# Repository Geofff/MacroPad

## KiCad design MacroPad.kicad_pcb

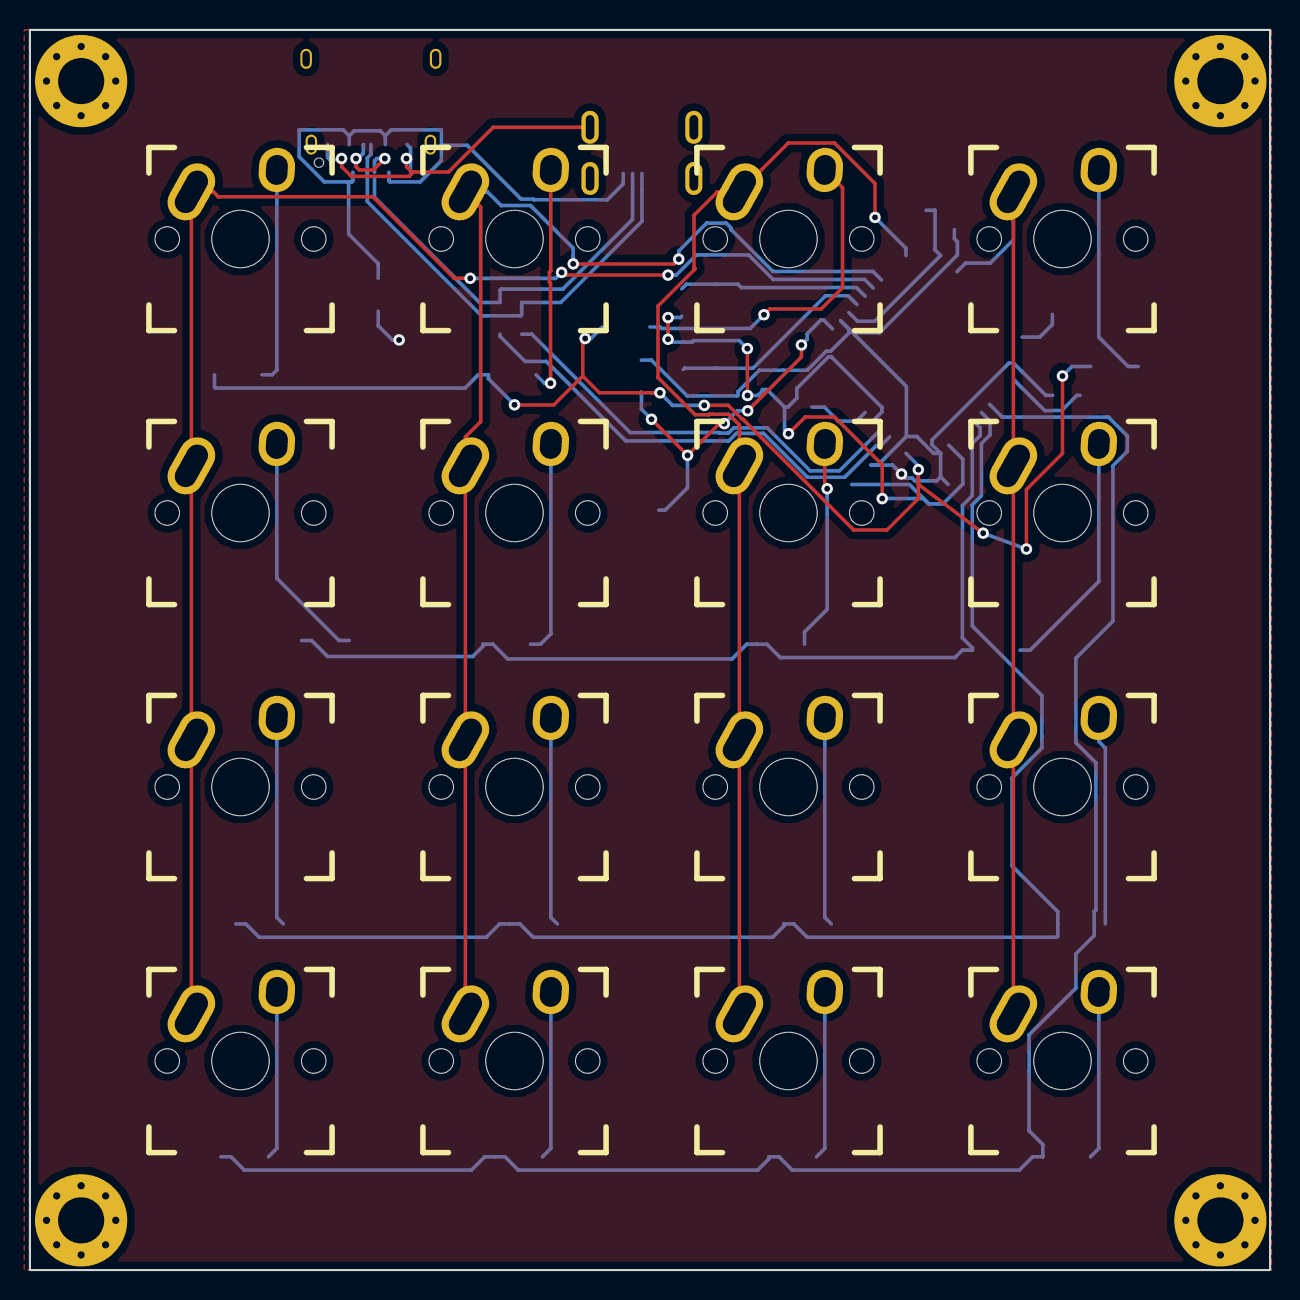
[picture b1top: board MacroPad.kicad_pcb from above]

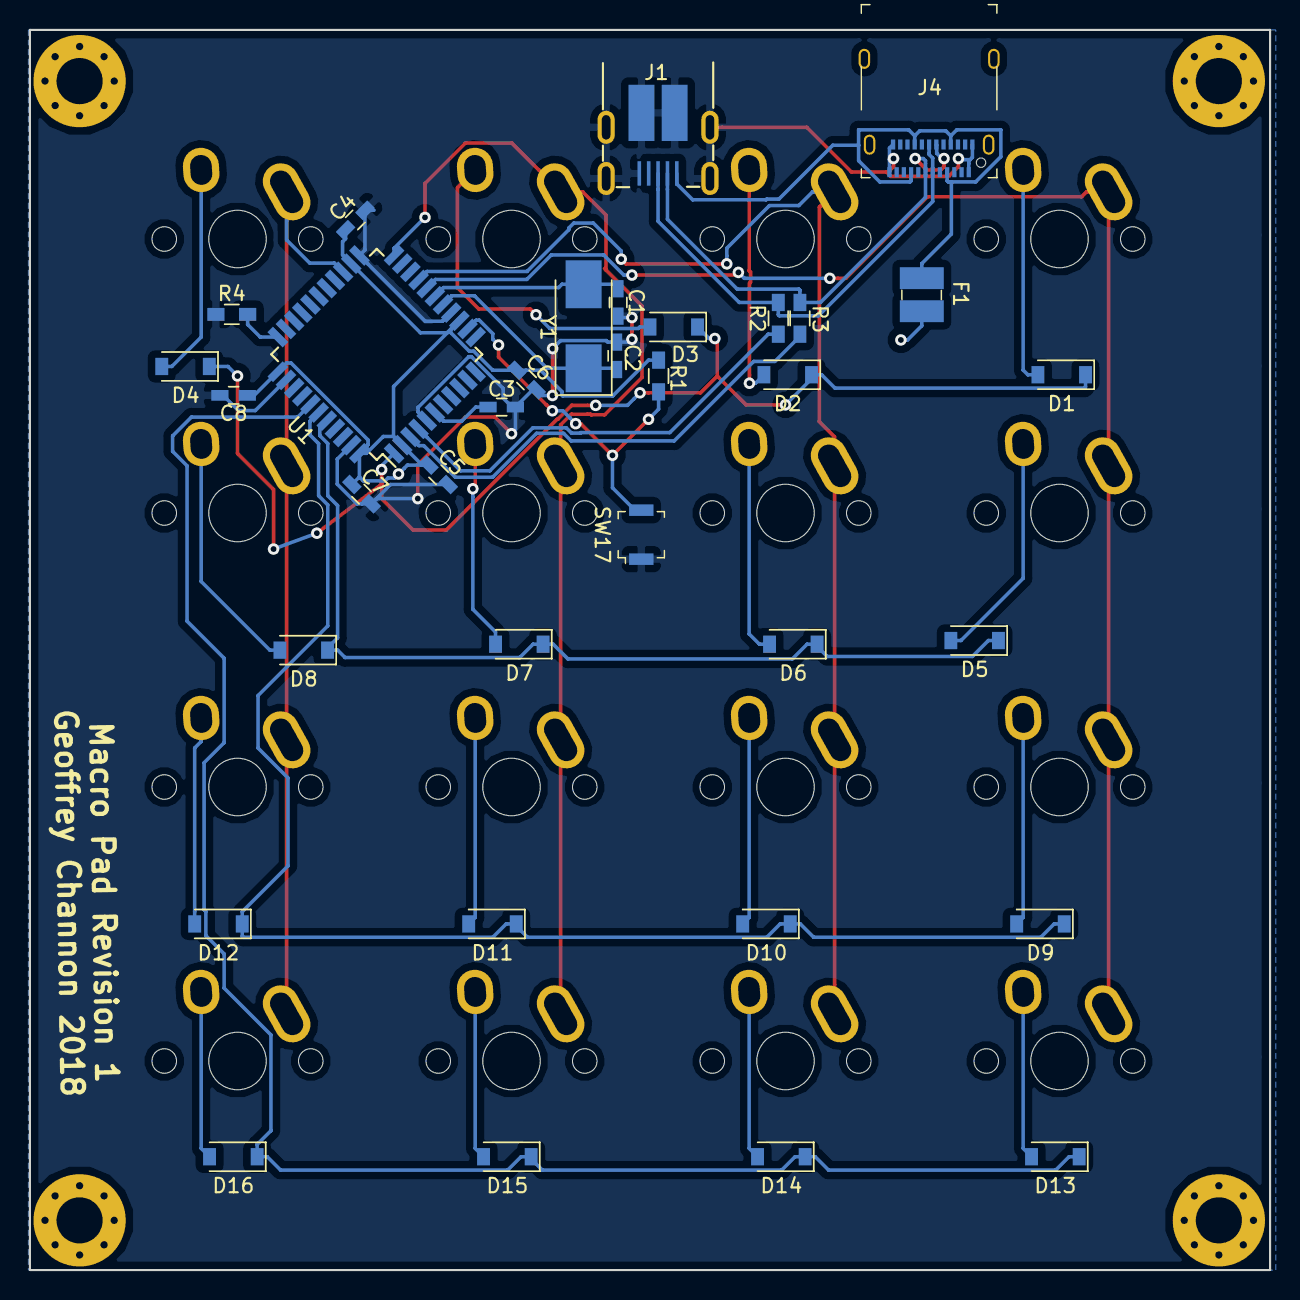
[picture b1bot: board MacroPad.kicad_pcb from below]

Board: 2 copper layers, 86.0 x 86.0 mm, 50 parts (34 on the bottom side), 36 nets.

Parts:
C1, C2: 18pF; C_0603_HandSoldering
C3, C4, C5, C6, C7, C8: 0.1uF; C_0603_HandSoldering
D1, D2, D3, D4, D5, D6, D7, D8, D9, D10, D11, D12, D13, D14, D15, D16: D; D_SOD-123
F1: 500mA; 1210
J1: UJ2-MIBH-4-SMT-TR; USB_Micro_B_Male_UJ2-MIBH-4-SMT-TR
J4: 12401610E4_2A; USB_Type_C_Female__12401610E4_2A
R1, R4: 10k; R_0603_HandSoldering
R2, R3: 22; R_0603_HandSoldering
SW1, SW2, SW3, SW4, SW5, SW6, SW7, SW8, SW9, SW10, SW11, SW12, SW13, SW14, SW15, SW16: SW_Push; Mx_Alps_100
SW17: SW_Push; Switch_Tactile_SMD_B3U-1000P
U1: ATmega32U4; TQFP-44_10x10mm_Pitch0.8mm
Y1: 16MHz; Crystal_SMD_0603-2pin_6.0x3.5mm_HandSoldering

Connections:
/COL_0: D1.1, D2.1, D3.1, D4.1, U1.1
/COL_1: D5.1, D6.1, D7.1, D8.1, U1.40
/COL_2: D9.1, D10.1, D11.1, D12.1, U1.39
/COL_3: D13.1, D14.1, D15.1, D16.1, U1.38
/RAW_VCC: F1.2, J1.1, J4.A4, J4.A9, J4.B4, J4.B9
/ROW_0: SW1.1, SW5.1, SW9.1, SW13.1, U1.18
/ROW_1: SW2.1, SW6.1, SW10.1, SW14.1, U1.19
/ROW_2: SW3.1, SW7.1, SW11.1, SW15.1, U1.22
/ROW_3: SW4.1, SW8.1, SW12.1, SW16.1, U1.25
GND: C1.2, C2.2, C3.2, C4.2, C5.2, C6.2, C7.2, C8.2, J1.5, J4.A1, J4.A12, J4.B1, J4.B12, R4.1, SW17.1, U1.5, U1.15, U1.23, U1.35, U1.43
unnamed: C1.1, U1.17, Y1.2
unnamed: C2.1, U1.16, Y1.1
unnamed: C3.1, U1.6
unnamed: D1.2, SW1.2
unnamed: D2.2, SW2.2
unnamed: D3.2, SW3.2
unnamed: D4.2, SW4.2
unnamed: D5.2, SW5.2
unnamed: D6.2, SW6.2
unnamed: D7.2, SW7.2
unnamed: D8.2, SW8.2
unnamed: D9.2, SW9.2
unnamed: D10.2, SW10.2
unnamed: D11.2, SW11.2
unnamed: D12.2, SW12.2
unnamed: D13.2, SW13.2
unnamed: D14.2, SW14.2
unnamed: D15.2, SW15.2
unnamed: D16.2, SW16.2
unnamed: R1.1, SW17.2, U1.13
unnamed: R2.1, U1.4
unnamed: R3.1, U1.3
unnamed: R4.2, U1.33
USB_A_D+: J1.3, J4.A6, J4.B6, R2.2
USB_A_D-: J1.2, J4.A7, J4.B7, R3.2
VCC: C4.1, C5.1, C6.1, C7.1, C8.1, F1.1, R1.2, U1.2, U1.14, U1.24, U1.34, U1.44

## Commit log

2018-06-10 Kicad commit
